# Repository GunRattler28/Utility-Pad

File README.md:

# Utility Pad

## Bill of Materials

| Id | Designator | Footprint | Quantity | Designation | Supplier and ref |

| 1 | J1 | ER_OLEDM0.91_1x-I2C | 1 | Conn_01x04_Socket | |

| 2 | SW1, SW2, SW3, SW4, SW5, SW6 | SW_Cherry_MX_1.00u_PCB | 6 | SW_Push | |

| 3 | SW7 | RotaryEncoder_Alps_EC11E-Switch_Vertical_H20mm | 1 | RotaryEncoder_Switch | |

| 4 | U1 | XIAO-Generic-Hybrid-14P-2.54-21X17.8MM | 1 | MOUDLE-SEEEDUINO-XIAO | |

## Renders and Screenshots

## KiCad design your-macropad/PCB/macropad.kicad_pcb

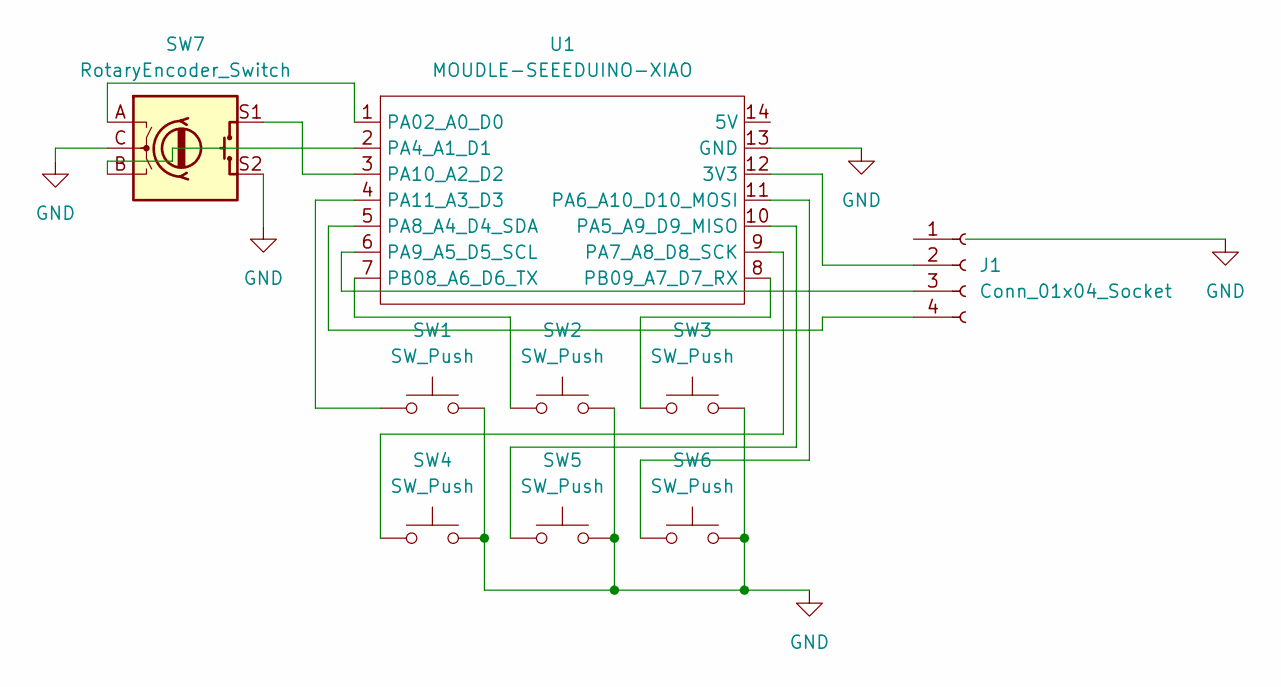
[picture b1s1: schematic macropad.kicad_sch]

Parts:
J1: Conn_01x04_Socket; ER_OLEDM0.91_1x-I2C
SW1, SW2, SW3, SW4, SW5, SW6: SW_Push; SW_Cherry_MX_1.00u_PCB
SW7: RotaryEncoder_Switch; RotaryEncoder_Alps_EC11E-Switch_Vertical_H20mm
U1: MOUDLE-SEEEDUINO-XIAO; XIAO-Generic-Hybrid-14P-2.54-21X17.8MM

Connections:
GND: SW1.2, SW2.2, SW3.2, SW4.2, SW5.2, SW6.2, SW7.C, SW7.S2, U1.13 (GND)
unnamed: J1.2, U1.12 (3V3)
unnamed: J1.3, U1.6 (PA9_A5_D5_SCL)
unnamed: J1.4, U1.5 (PA8_A4_D4_SDA)
unnamed: SW7.A, U1.1 (PA02_A0_D0)
unnamed: SW7.B, U1.2 (PA4_A1_D1)
unnamed: SW5.1, U1.10 (PA5_A9_D9_MISO)
unnamed: SW6.1, U1.11 (PA6_A10_D10_MOSI)
unnamed: SW4.1, U1.9 (PA7_A8_D8_SCK)
unnamed: SW7.S1, U1.3 (PA10_A2_D2)
unnamed: SW1.1, U1.4 (PA11_A3_D3)
unnamed: SW2.1, U1.7 (PB08_A6_D6_TX)
unnamed: SW3.1, U1.8 (PB09_A7_D7_RX)

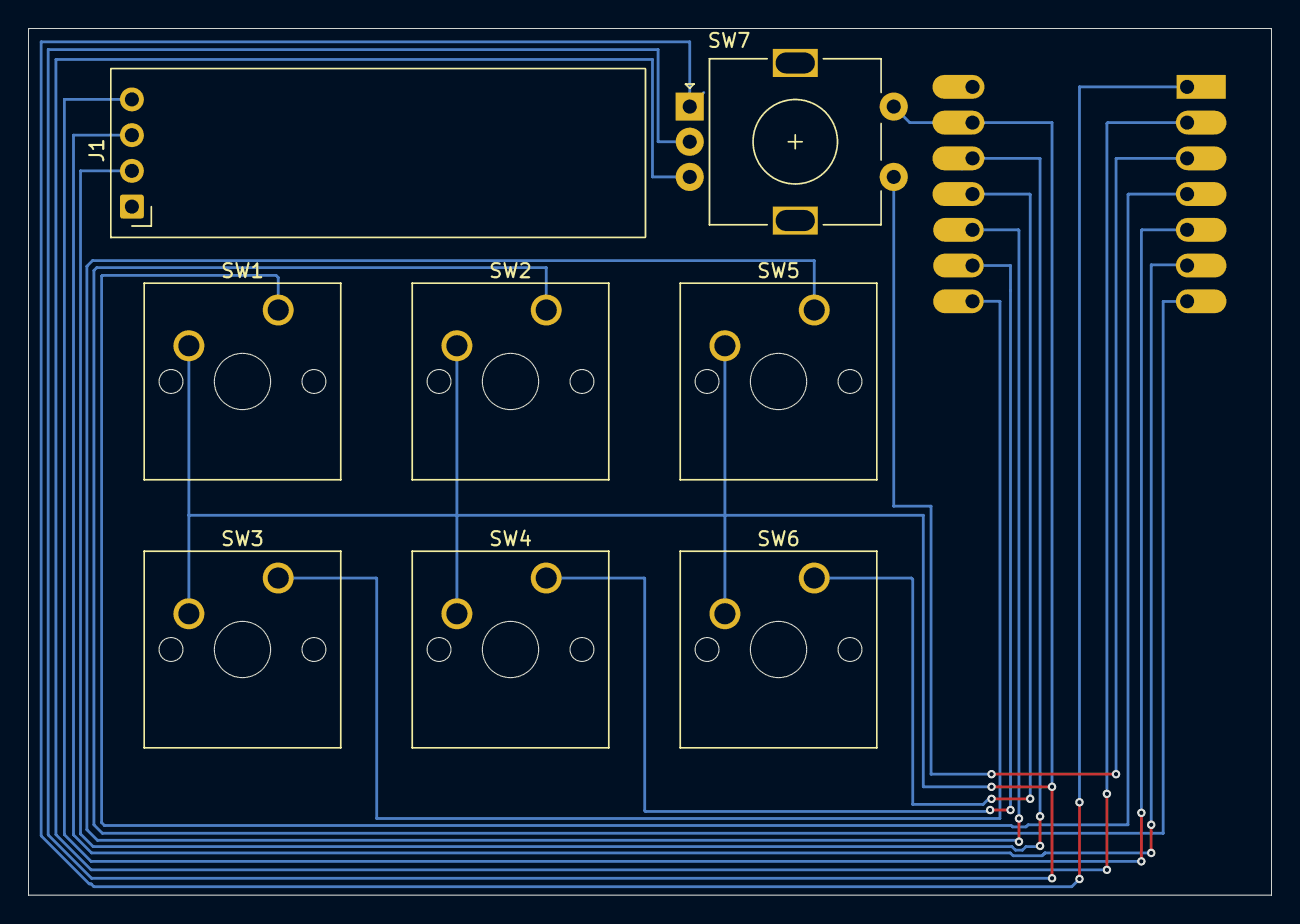
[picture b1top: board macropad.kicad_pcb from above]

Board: 2 copper layers, 88.3 x 61.6 mm, 9 parts (1 on the bottom side), 13 nets.

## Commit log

2026-06-27 Format README.md for consistency
